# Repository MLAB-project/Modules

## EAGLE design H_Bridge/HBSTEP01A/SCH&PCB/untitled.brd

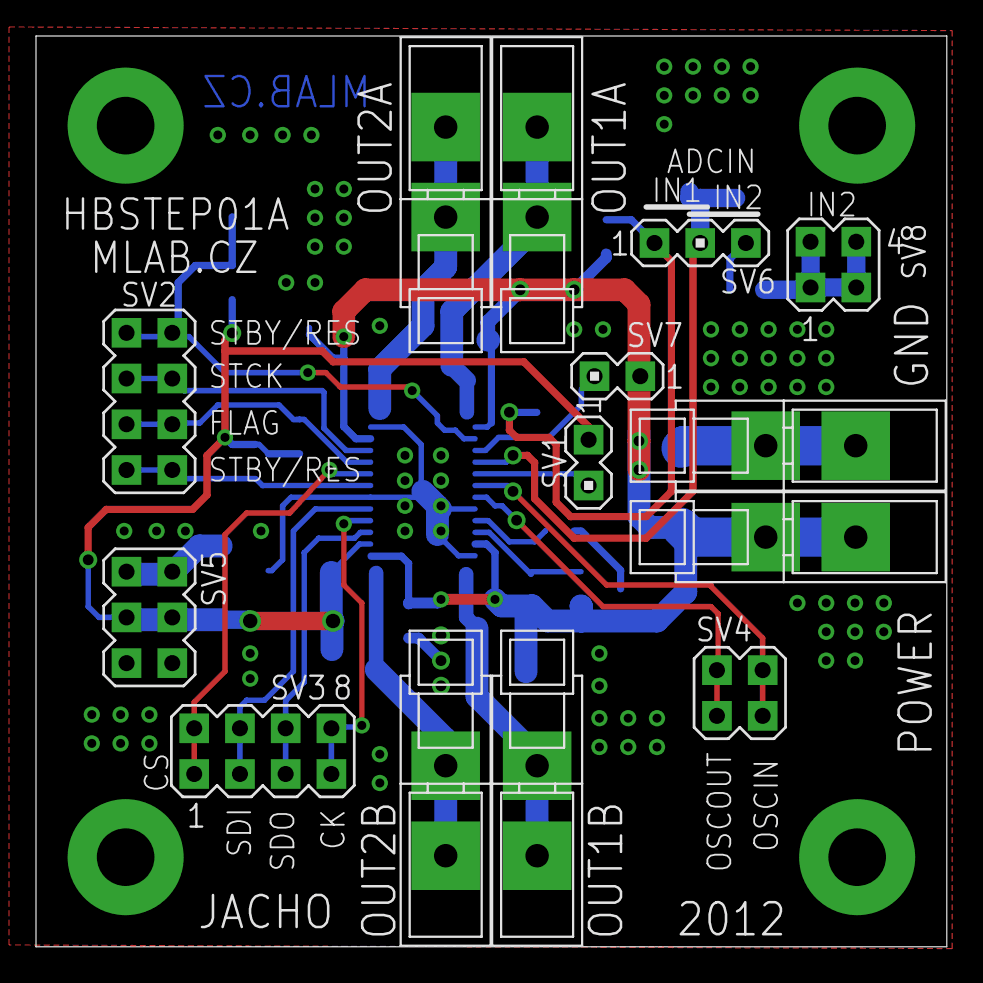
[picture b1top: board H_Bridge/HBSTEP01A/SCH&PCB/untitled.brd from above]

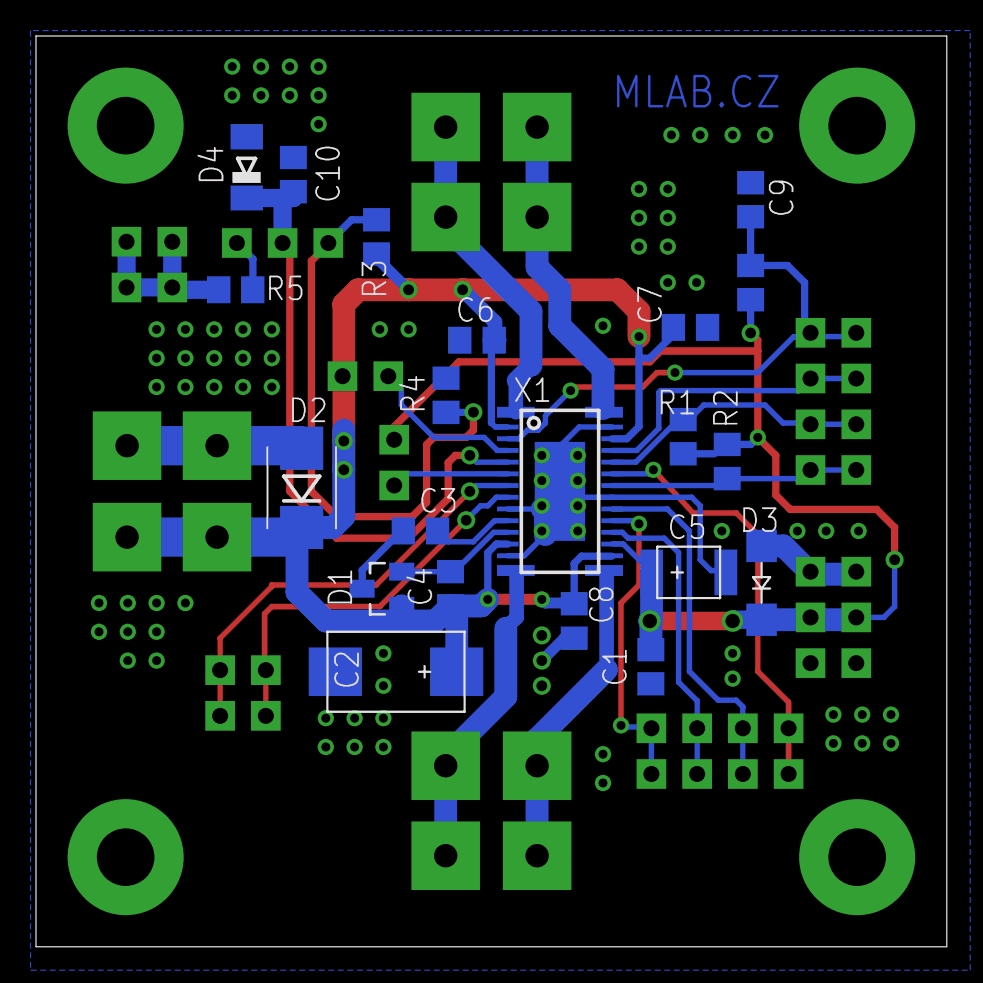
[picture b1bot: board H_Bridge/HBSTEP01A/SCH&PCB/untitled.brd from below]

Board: 2 copper layers, 50.6 x 50.6 mm, 39 parts (21 on the bottom side), 26 nets.

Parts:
C1, C3, C4, C6, C7, C8, C10: C0805
C2: 22M/20V; D
C5: 1M/35V; B
C9: 100p; C0805
CON1, CON2, CON3, CON4, CON5, CON6: WAGO256
D1: SOT23
D2: SMB
D3: SMA
D4: MINIMELF
R1, R2, R3, R4, R5, R5-PULLUP: R0805
SV1, SV7: MA02-1
SV2: MA04-2
SV3: MA04-2@1
SV4: MA02-2
SV5: MA03-2
SV6: MA03-1
SV8: MA02-2@1
X1: HTSSOP28
X3, X4, X5, X6: SROUB3M

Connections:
+12V: C2.+, C4.1, C6.1, C7.1, C8.1, CON6.1, CON6.A1, D1.1, D2.K, R3.2, X1.2, X1.12, X1.16, X1.26
ADCIN: C10.1, D4.C, SV6.2, X1.5
GND: C1.2, C2.-, C5.-, C6.2, C7.2, C8.2, C9.2, C10.2, CON5.1, CON5.A1, D2.A, D3.A, D4.A, R4.1, SV5.1, SV5.2, SV5.5, SV5.6, SV7.1, X1.9, X1.13, X1.21, X1.27, X1.P$1, X3.P$1, X4.P$1, X5.P$1, X6.P$1
unnamed: R1.1, SV2.5, SV2.6, X1.24
unnamed: R2.1, SV2.7, SV2.8, X1.22
unnamed: SV2.3, SV2.4, X1.25
unnamed: C9.1, R5-PULLUP.1, SV2.1, SV2.2, X1.3
unnamed: SV3.1, SV3.2, X1.23
unnamed: SV3.3, SV3.4, X1.20
unnamed: SV3.5, SV3.6, X1.18
unnamed: SV1.2, X1.6
unnamed: SV7.2, X1.4
unnamed: SV4.3, SV4.4, X1.7
unnamed: CON4.1, CON4.A1, X1.28
unnamed: CON3.1, CON3.A1, X1.1
unnamed: CON1.1, CON1.A1, X1.14
unnamed: CON2.1, CON2.A1, X1.15
unnamed: SV4.1, SV4.2, X1.8
unnamed: SV3.7, SV3.8, X1.19
unnamed: R3.1, R4.2, SV6.1
unnamed: R5.2, SV6.3
unnamed: C4.2, D1.2, X1.11
unnamed: C3.2, D1.3
unnamed: C3.1, X1.10
unnamed: R5.1, SV8.1, SV8.2, SV8.3, SV8.4
VCC: C1.1, C5.+, D3.K, R1.2, R2.2, R5-PULLUP.2, SV1.1, SV5.3, SV5.4, X1.17

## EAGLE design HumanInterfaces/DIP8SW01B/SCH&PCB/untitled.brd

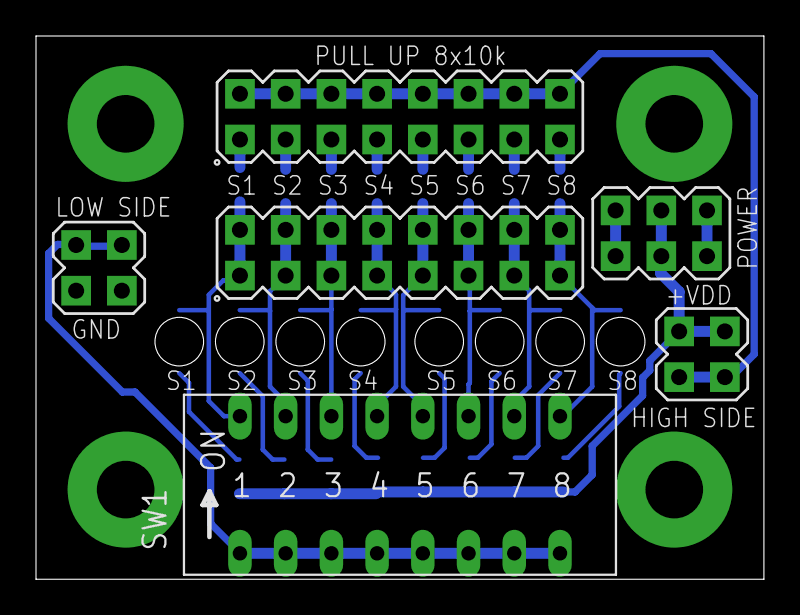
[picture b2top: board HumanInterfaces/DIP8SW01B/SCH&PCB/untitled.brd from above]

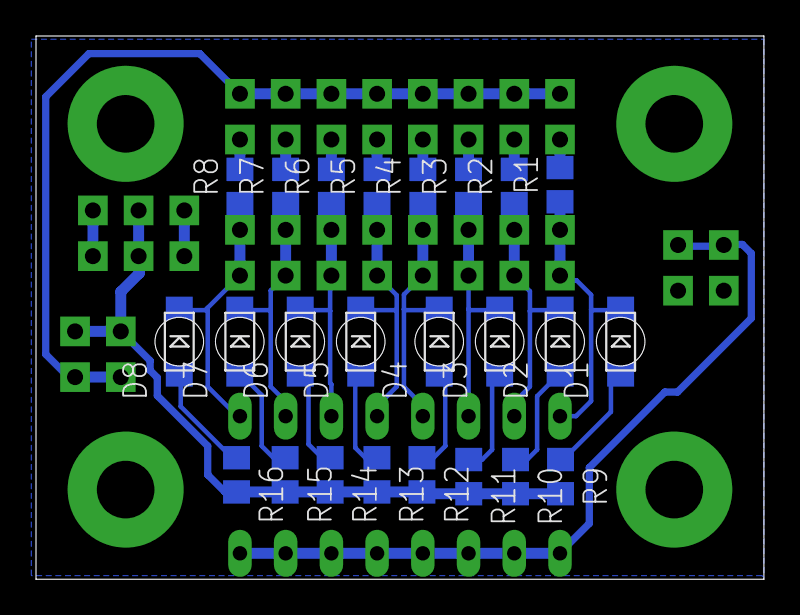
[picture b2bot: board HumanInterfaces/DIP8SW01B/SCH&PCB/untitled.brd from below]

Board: 2 copper layers, 40.4 x 30.2 mm, 34 parts (24 on the bottom side), 28 nets.

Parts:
D1, D2, D3, D4, D5, D6, D7, D8: 1206_2
R1, R2, R3, R4, R5, R6, R7, R8: 10k; 0805
R9, R10, R11, R12, R13, R14, R15, R16: 0805
SV1: MA08-2
SV2, SV4: MA02-2
SV3: MA03-2
SW1: DIP08SW
SW2: MA08-2
X1, X2, X3, X4: SROUB3M

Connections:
GND: SV3.1, SV3.2, SV3.5, SV3.6, SV4.3, SV4.4, X1.P$1, X2.P$1, X3.P$1, X4.P$1
unnamed: D1.K, R1.1, SV1.1, SV1.2, SW1.16
unnamed: D2.K, R2.1, SV1.3, SV1.4, SW1.15
unnamed: D3.K, R3.1, SV1.5, SV1.6, SW1.14
unnamed: D4.K, R4.1, SV1.7, SV1.8, SW1.13
unnamed: D5.K, R5.1, SV1.9, SV1.10, SW1.12
unnamed: D6.K, R6.1, SV1.11, SV1.12, SW1.11
unnamed: D7.K, R7.1, SV1.13, SV1.14, SW1.10
unnamed: D8.K, R8.1, SV1.15, SV1.16, SW1.9
unnamed: R1.2, SW2.1
unnamed: R2.2, SW2.3
unnamed: R3.2, SW2.5
unnamed: R4.2, SW2.7
unnamed: R5.2, SW2.9
unnamed: R6.2, SW2.11
unnamed: R7.2, SW2.13
unnamed: R8.2, SW2.15
unnamed: D2.A, R10.1
unnamed: D3.A, R11.1
unnamed: D4.A, R12.1
unnamed: SV2.1, SV2.2, SW2.2, SW2.4, SW2.6, SW2.8, SW2.10, SW2.12, SW2.14, SW2.16
unnamed: D5.A, R13.1
unnamed: SV4.1, SV4.2, SW1.1, SW1.2, SW1.3, SW1.4, SW1.5, SW1.6, SW1.7, SW1.8
unnamed: D6.A, R14.1
unnamed: D7.A, R15.1
unnamed: D1.A, R9.1
unnamed: D8.A, R16.1
VCC: R9.2, R10.2, R11.2, R12.2, R13.2, R14.2, R15.2, R16.2, SV2.3, SV2.4, SV3.3, SV3.4

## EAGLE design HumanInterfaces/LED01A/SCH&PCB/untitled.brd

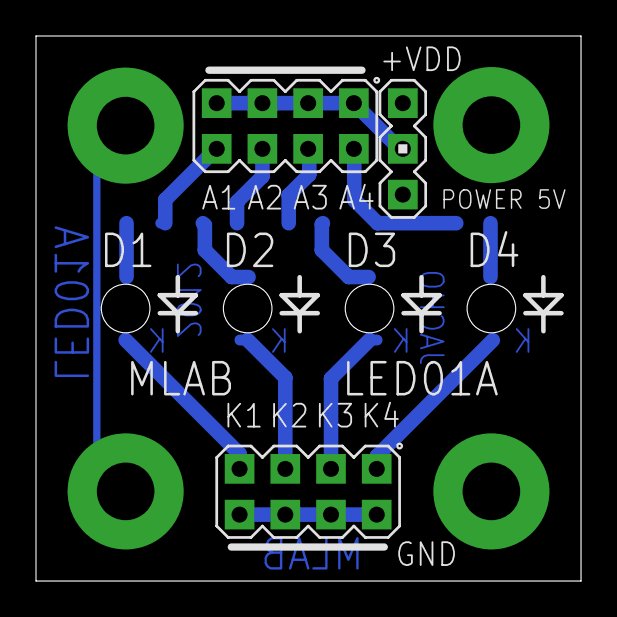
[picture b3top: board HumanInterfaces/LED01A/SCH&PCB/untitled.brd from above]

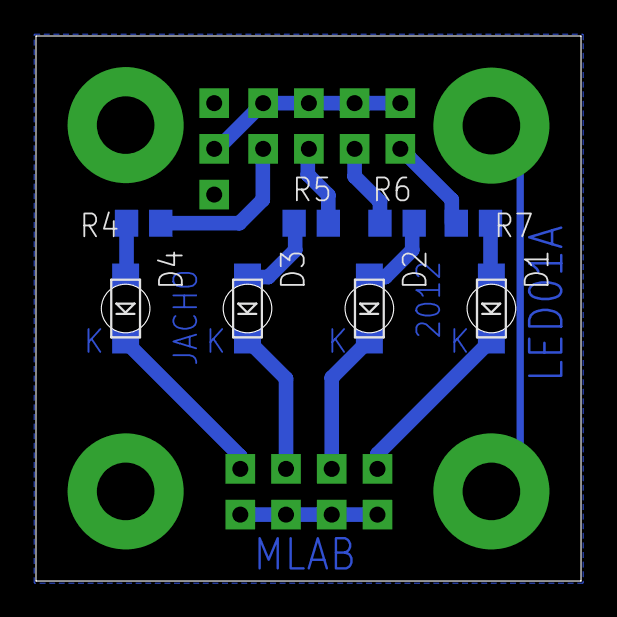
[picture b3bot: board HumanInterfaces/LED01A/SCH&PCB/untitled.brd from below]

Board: 2 copper layers, 30.3 x 30.3 mm, 15 parts (8 on the bottom side), 14 nets.

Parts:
D1, D2, D3, D4: 1206
R4, R5, R6, R7: 0805
SV1, SV2: MA04-2
SV3: MA03-1
X1, X2, X3, X4: SROUB3M

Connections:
GND: SV1.2, SV1.4, SV1.6, SV1.8, SV3.1, SV3.3, X1.P$1, X2.P$1, X3.P$1, X4.P$1
unnamed: D4.K, SV1.1
unnamed: D4.A, R4.1
unnamed: D3.K, SV1.3
unnamed: D2.K, SV1.5
unnamed: D3.A, R5.1
unnamed: D2.A, R6.1
unnamed: D1.A, R7.1
unnamed: R4.2, SV2.2
unnamed: R5.2, SV2.4
unnamed: R6.2, SV2.6
unnamed: D1.K, SV1.7
unnamed: SV2.1, SV2.3, SV2.5, SV2.7, SV3.2
unnamed: R7.2, SV2.8

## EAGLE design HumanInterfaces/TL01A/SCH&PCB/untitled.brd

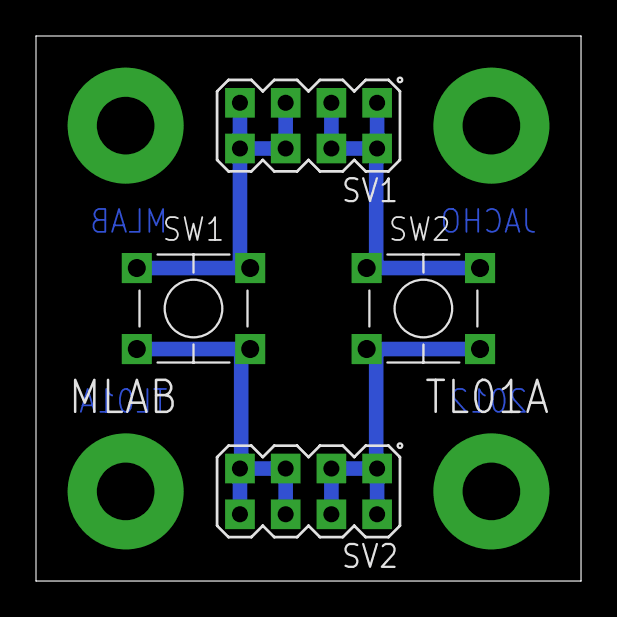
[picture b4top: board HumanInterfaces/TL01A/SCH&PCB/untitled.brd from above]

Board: 2 copper layers, 30.3 x 30.3 mm, 8 parts (0 on the bottom side), 5 nets.

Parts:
SV1, SV2: MA04-2
SW1, SW2: TACT-64K
X1, X2, X3, X4: SROUB3M

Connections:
GND: X1.P$1, X2.P$1, X3.P$1, X4.P$1
unnamed: SV1.5, SV1.6, SV1.7, SV1.8, SW1.P$1, SW1.P$2
unnamed: SV2.5, SV2.6, SV2.7, SV2.8, SW1.P$3, SW1.P$4
unnamed: SV1.1, SV1.2, SV1.3, SV1.4, SW2.P$1, SW2.P$2
unnamed: SV2.1, SV2.2, SV2.3, SV2.4, SW2.P$3, SW2.P$4

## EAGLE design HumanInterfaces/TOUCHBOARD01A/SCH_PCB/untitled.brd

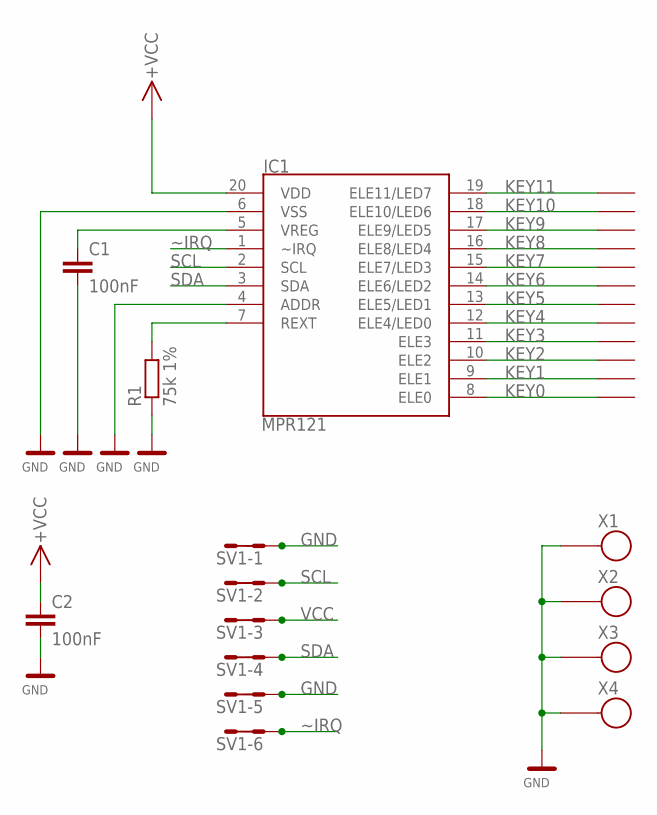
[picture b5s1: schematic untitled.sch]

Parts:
C1, C2: 100nF; C0805
IC1: MPR121; QFN-20-0.4MM
R1: 75k 1%; 0805
SV1: MA06-2
U$1, U$2, U$3, U$4, U$5, U$6, U$7, U$8, U$9, U$10, U$11, U$12: TL_DOTYK_10_15; PLOSKA10_15
X1, X2, X3, X4: SROUB3M

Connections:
GND: C1.2, C2.2, IC1.4 (ADDR), IC1.6 (VSS), R1.1, SV1.1, SV1.2, SV1.9, SV1.10, X1.P$1, X2.P$1, X3.P$1, X4.P$1
KEY0: IC1.8 (ELE0), U$1.P$1
KEY1: IC1.9 (ELE1), U$2.P$1
KEY2: IC1.10 (ELE2), U$3.P$1
KEY3: IC1.11 (ELE3), U$4.P$1
KEY4: IC1.12 (ELE4/LED0), U$5.P$1
KEY5: IC1.13 (ELE5/LED1), U$6.P$1
KEY6: IC1.14 (ELE6/LED2), U$7.P$1
KEY7: IC1.15 (ELE7/LED3), U$8.P$1
KEY8: IC1.16 (ELE8/LED4), U$9.P$1
KEY9: IC1.17 (ELE9/LED5), U$10.P$1
KEY10: IC1.18 (ELE10/LED6), U$11.P$1
KEY11: IC1.19 (ELE11/LED7), U$12.P$1
REXT: IC1.7 (REXT), R1.2
SCL: IC1.2 (SCL), SV1.3, SV1.4
SDA: IC1.3 (SDA), SV1.7, SV1.8
VCC: C2.1, IC1.20 (VDD), SV1.5, SV1.6
VREG: C1.1, IC1.5 (VREG)
~IRQ: IC1.1 (~IRQ), SV1.11, SV1.12

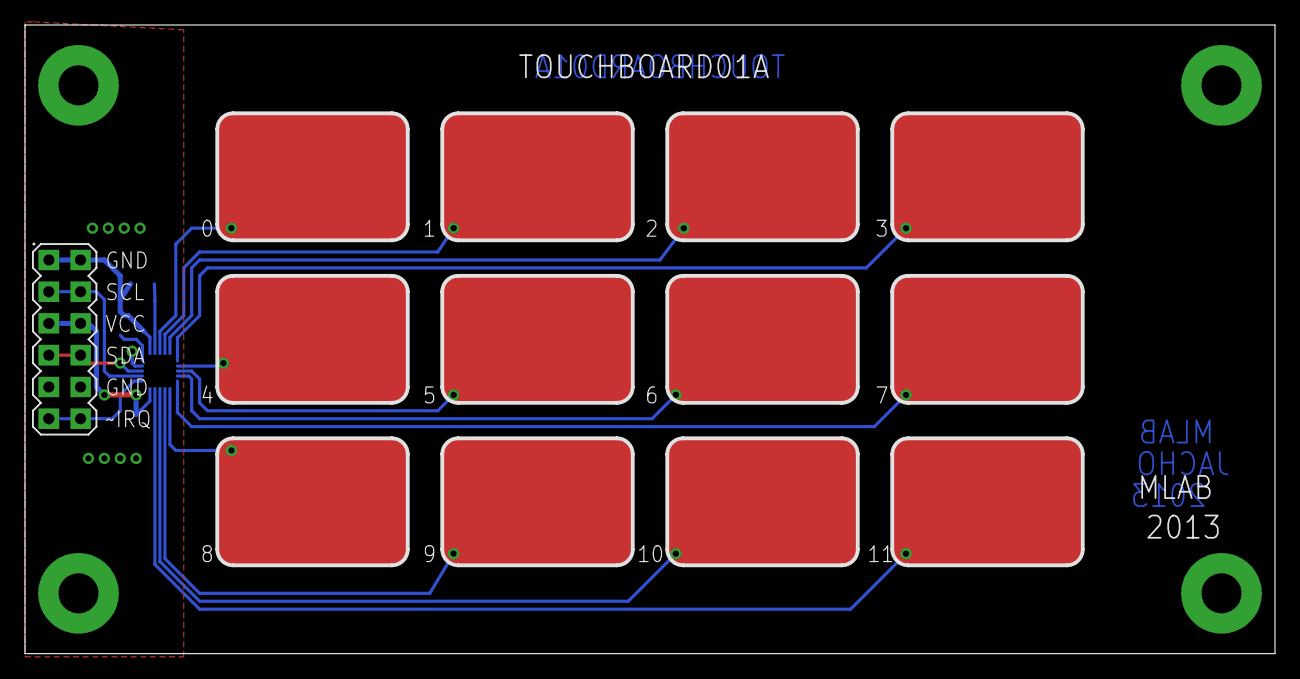
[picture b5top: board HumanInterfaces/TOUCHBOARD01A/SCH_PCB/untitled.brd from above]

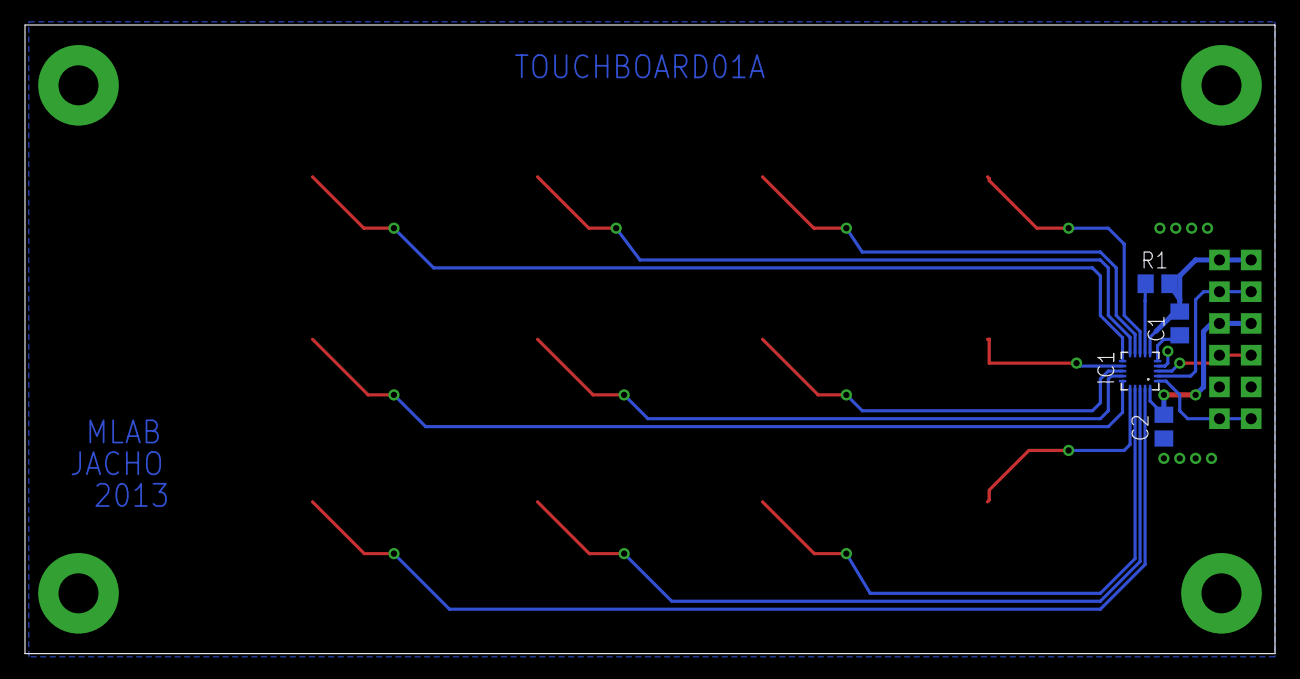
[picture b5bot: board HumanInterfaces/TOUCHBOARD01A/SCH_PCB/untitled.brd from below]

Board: 2 copper layers, 100.0 x 50.3 mm, 21 parts (4 on the bottom side), 19 nets.

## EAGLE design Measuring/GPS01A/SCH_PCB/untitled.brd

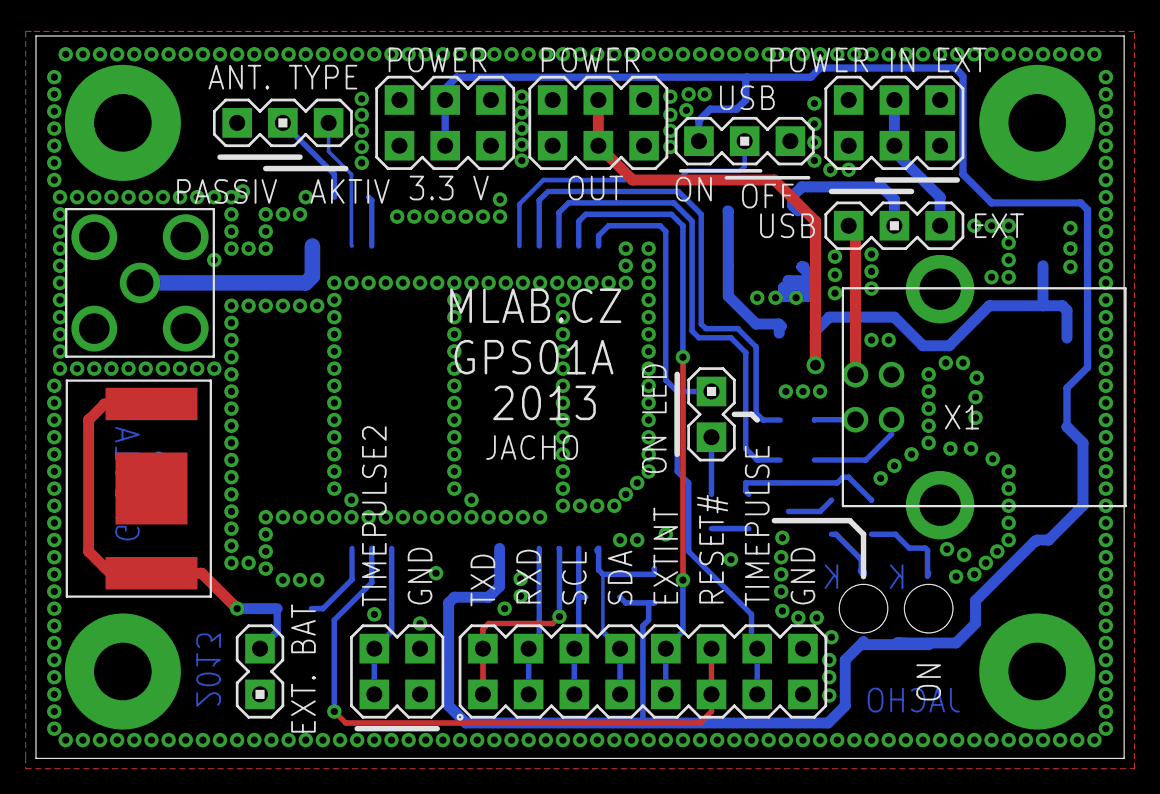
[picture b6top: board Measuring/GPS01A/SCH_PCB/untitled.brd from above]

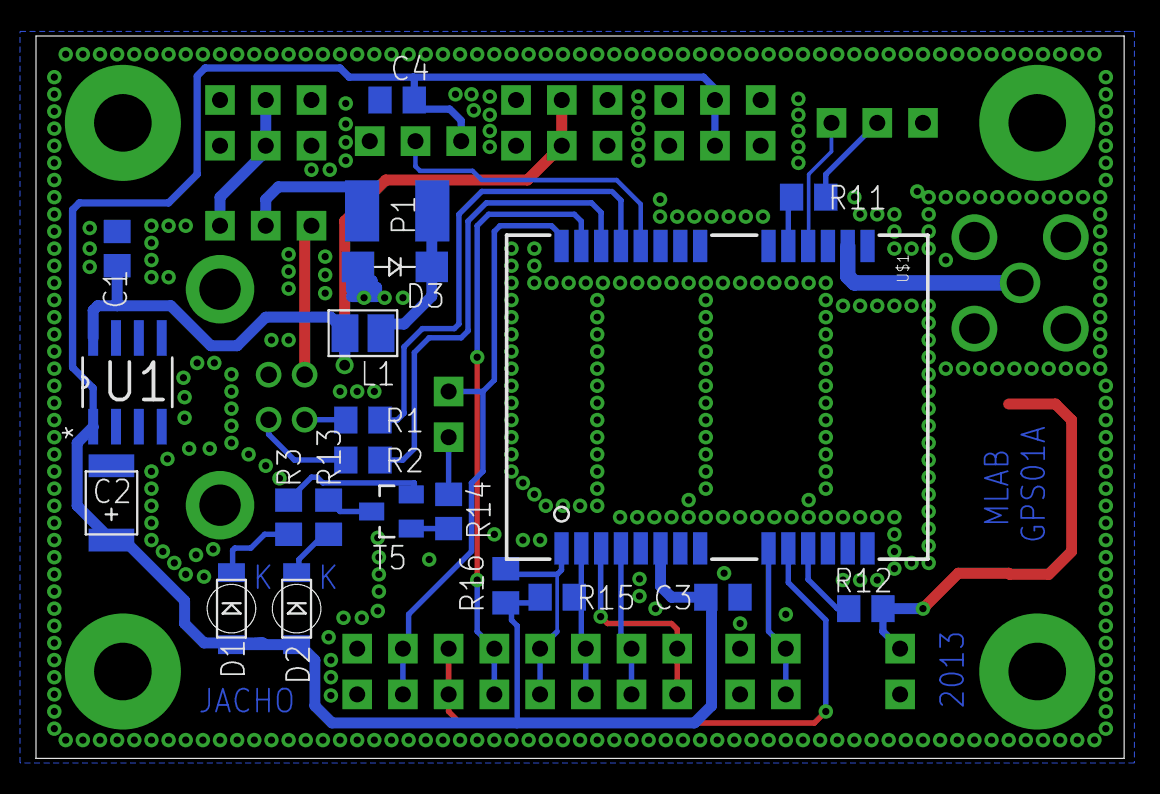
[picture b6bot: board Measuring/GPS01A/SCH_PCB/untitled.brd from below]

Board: 2 copper layers, 60.5 x 40.1 mm, 38 parts (21 on the bottom side), 31 nets.

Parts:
C1, C3, C4: 100nF; C0805
C2: 10uF; B
D1: CERVENA; 1206
D2: ZELENA; 1206
D3: SMA
L1: 1210
P1: 1812
R1, R2: 33; 0805
R3, R13: 150R; 0805
R11: 10; 0805
R12: 100; 0805
R14: 0805
R15, R16: 4k7; 0805
SV1, SV4, SV8: MA03-1
SV2, SV9, SV10: MA03-2
SV3, SV7: MA02-1
SV5: MA02-2
SV6: MA08-2
SW1: 1.55V; BAT6MM8
SW2: SMA
T5: BC817; SOT23
U1: LE33CD-TR; SOIC127P600X175-8N
U$1: UBLOX-LEA-6
X1: USB_B
X2, X3, X4, X5: SROUB3M

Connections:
+3.3V: C2.+, C3.1, C4.1, D1.A, D2.A, R15.2, R16.2, SV8.1, SV9.3, SV9.4, U1.1, U$1.6
EXTINT: SV6.9, SV6.10, U$1.27
GND: C1.2, C2.-, C3.2, C4.2, D3.A, R3.1, SV2.1, SV2.2, SV2.5, SV2.6, SV3.2, SV4.1, SV5.3, SV5.4, SV6.15, SV6.16, SV8.3, SV9.1, SV9.2, SV9.5, SV9.6, SV10.1, SV10.2, SV10.5, SV10.6, SW1.-, SW2.-1, SW2.-2, SW2.-3, SW2.-4, T5.2, U1.2, U1.3, U1.5, U1.6, U1.7, U$1.7, U$1.13, U$1.14, U$1.15, U$1.17, X1.4, X1.GND, X1.GND2, X2.P$1, X3.P$1, X4.P$1, X5.P$1
unnamed: SW2.+, U$1.16
unnamed: SV1.1, SV2.3, SV2.4
unnamed: R1.1, X1.2
unnamed: R2.1, X1.3
unnamed: C1.1, L1.P$2, SV10.3, SV10.4, U1.8
unnamed: P1.2, SV1.2
unnamed: D1.K, R3.2
unnamed: R11.2, U$1.19
unnamed: D3.K, L1.P$1, P1.1
unnamed: R11.1, SV4.2
unnamed: R12.1, U$1.11
unnamed: R12.2, SV3.1, SW1.1+, SW1.2+
unnamed: SV5.1, SV5.2, U$1.9
unnamed: D2.K, R13.2
unnamed: R13.1, T5.3
unnamed: R14.2, T5.1
unnamed: R14.1, SV7.1
RESET_N: SV6.11, SV6.12, U$1.10
RXD: SV6.3, SV6.4, U$1.4
SCL: R15.1, SV6.5, SV6.6, U$1.2
SDA: R16.1, SV6.7, SV6.8, U$1.1
TIMEPULSE: SV6.13, SV6.14, SV7.2, U$1.28
TXD: SV6.1, SV6.2, U$1.3
USB_DET: SV8.2, U$1.24
USB_DM: R1.2, U$1.25
USB_DP: R2.2, U$1.26
VCC_RF: SV4.3, U$1.18
VDD_USB: SV1.3, X1.1

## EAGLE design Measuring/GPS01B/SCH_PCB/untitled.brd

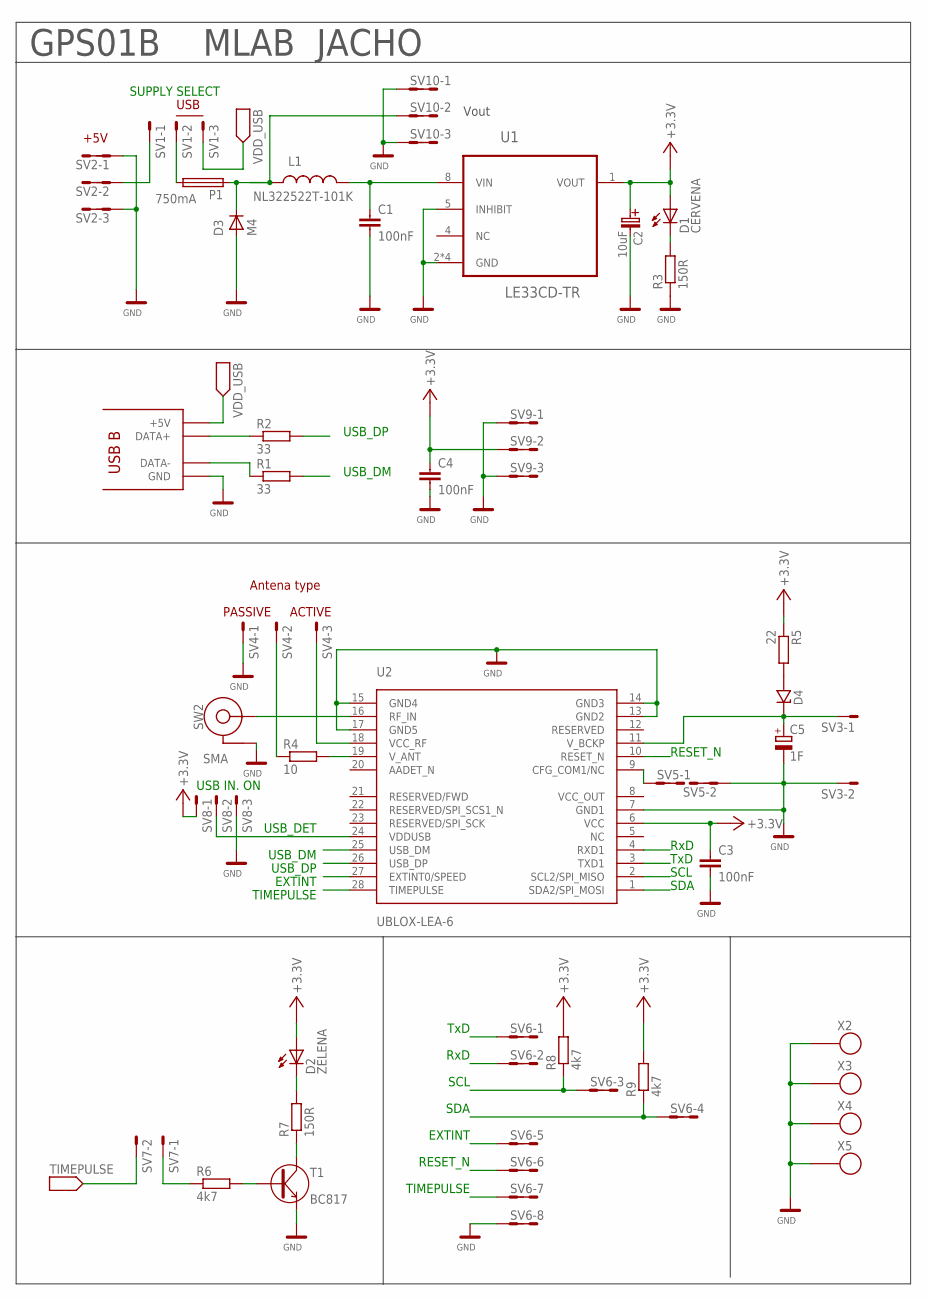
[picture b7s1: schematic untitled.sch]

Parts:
C1, C3, C4: 100nF; C0805
C2: 10uF; B
C5: 1F; E3,5-8
D1: CERVENA; 1206
D2: ZELENA; 1206
D3: M4; SMA
D4: D-ZENEROVA; MINIMELF
L1: NL322522T-101K; 1210
P1: 750mA; 1812
R1, R2: 33; 0805
R3, R7: 150R; 0805
R4: 10; 0805
R5: 22; 0805
R6, R8, R9: 4k7; 0805
SV1, SV4, SV8: MA03-1
SV2, SV9, SV10: MA03-2
SV3, SV7: MA02-1
SV5: MA02-2
SV6: MA08-2
SW2: SMA
T1: BC817; SOT23
U1: LE33CD-TR; SOIC127P600X175-8N
U2: UBLOX-LEA-6
X1: USB_B
X2, X3, X4, X5: SROUB3M

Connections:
+3.3V: C2.+ (C_EL+), C3.1, C4.1, D1.A, D2.A, R5.1, R8.2, R9.2, SV8.1, SV9.3, SV9.4, U1.1 (VOUT), U2.6 (VCC)
EXTINT: SV6.9, SV6.10, U2.27 (EXTINT0/SPEED)
GND: C1.2, C2.- (C_EL-), C3.2, C4.2, C5.-, D3.A, R3.1, SV2.1, SV2.2, SV2.5, SV2.6, SV3.2, SV4.1, SV5.3, SV5.4, SV6.15, SV6.16, SV8.3, SV9.1, SV9.2, SV9.5, SV9.6, SV10.1, SV10.2, SV10.5, SV10.6, SW2.-1 (-), SW2.-2 (-), SW2.-3 (-), SW2.-4 (-), T1.2 (E), U1.2 (GND), U1.3 (GND), U1.5 (INHIBIT), U1.6 (GND), U1.7 (GND), U2.7 (GND1), U2.13 (GND2), U2.14 (GND3), U2.15 (GND4), U2.17 (GND5), X1.4 (GND), X1.GND, X1.GND2 (GND), X2.P$1, X3.P$1, X4.P$1, X5.P$1
unnamed: SW2.+, U2.16 (RF_IN)
unnamed: SV1.1, SV2.3, SV2.4
unnamed: R1.1, X1.2 (DATA-)
unnamed: R2.1, X1.3 (DATA+)
unnamed: C1.1, L1.P$2 (2), U1.8 (VIN)
unnamed: D4.A, R5.2
unnamed: P1.2, SV1.2
unnamed: D3.K (C), L1.P$1 (1), P1.1, SV10.3, SV10.4
unnamed: D1.K (C), R3.2
unnamed: R4.2, U2.19 (V_ANT)
unnamed: R4.1, SV4.2
unnamed: C5.+, D4.C (K), SV3.1, U2.11 (V_BCKP)
unnamed: SV5.1, SV5.2, U2.9 (CFG_COM1/NC)
unnamed: D2.K (C), R7.2
unnamed: R7.1, T1.3 (C)
unnamed: R6.2, T1.1 (B)
unnamed: R6.1, SV7.1
RESET_N: SV6.11, SV6.12, U2.10 (RESET_N)
RXD: SV6.3, SV6.4, U2.4 (RXD1)
SCL: R8.1, SV6.5, SV6.6, U2.2 (SCL2/SPI_MISO)
SDA: R9.1, SV6.7, SV6.8, U2.1 (SDA2/SPI_MOSI)
TIMEPULSE: SV6.13, SV6.14, SV7.2, U2.28 (TIMEPULSE)
TXD: SV6.1, SV6.2, U2.3 (TXD1)
USB_DET: SV8.2, U2.24 (VDDUSB)
USB_DM: R1.2, U2.25 (USB_DM)
USB_DP: R2.2, U2.26 (USB_DP)
VCC_RF: SV4.3, U2.18 (VCC_RF)
VDD_USB: SV1.3, X1.1 (+5V)

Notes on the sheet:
USB_DM
USB_DP
USB
+5V
TxD
RxD
Antena type
ACTIVE
PASSIVE
USB_DET
EXTINT
TIMEPULSE
RESET_N
SCL
SDA
SUPPLY SELECT
GPS01B
MLAB
JACHO
USB IN. ON
Vout

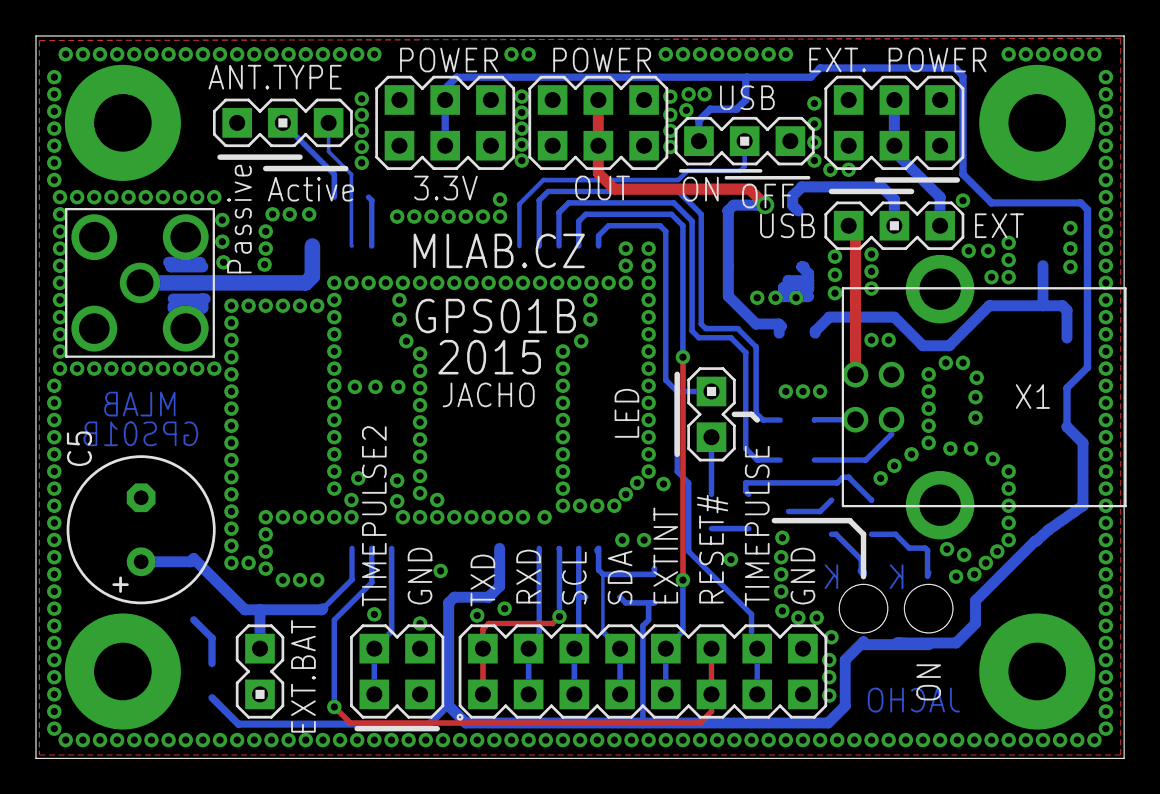
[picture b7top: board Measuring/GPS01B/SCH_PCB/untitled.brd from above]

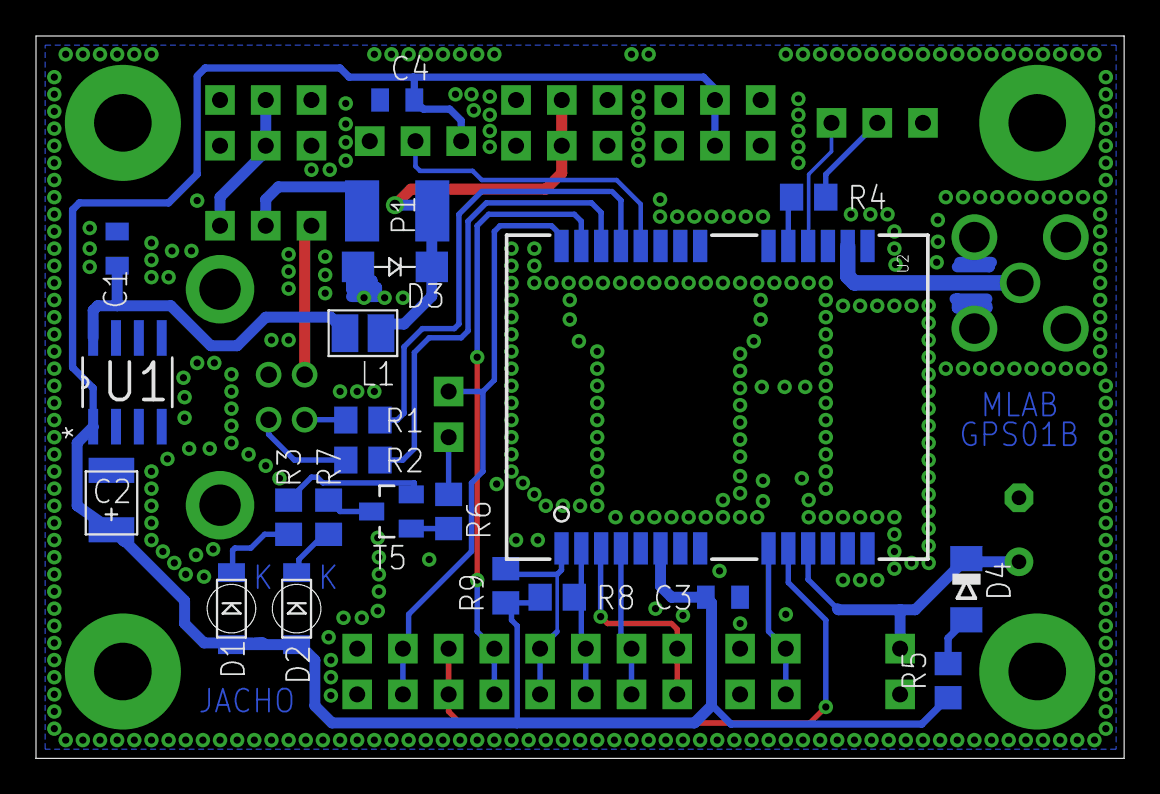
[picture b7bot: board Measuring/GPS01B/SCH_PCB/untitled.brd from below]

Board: 2 copper layers, 60.5 x 40.1 mm, 39 parts (22 on the bottom side), 31 nets.

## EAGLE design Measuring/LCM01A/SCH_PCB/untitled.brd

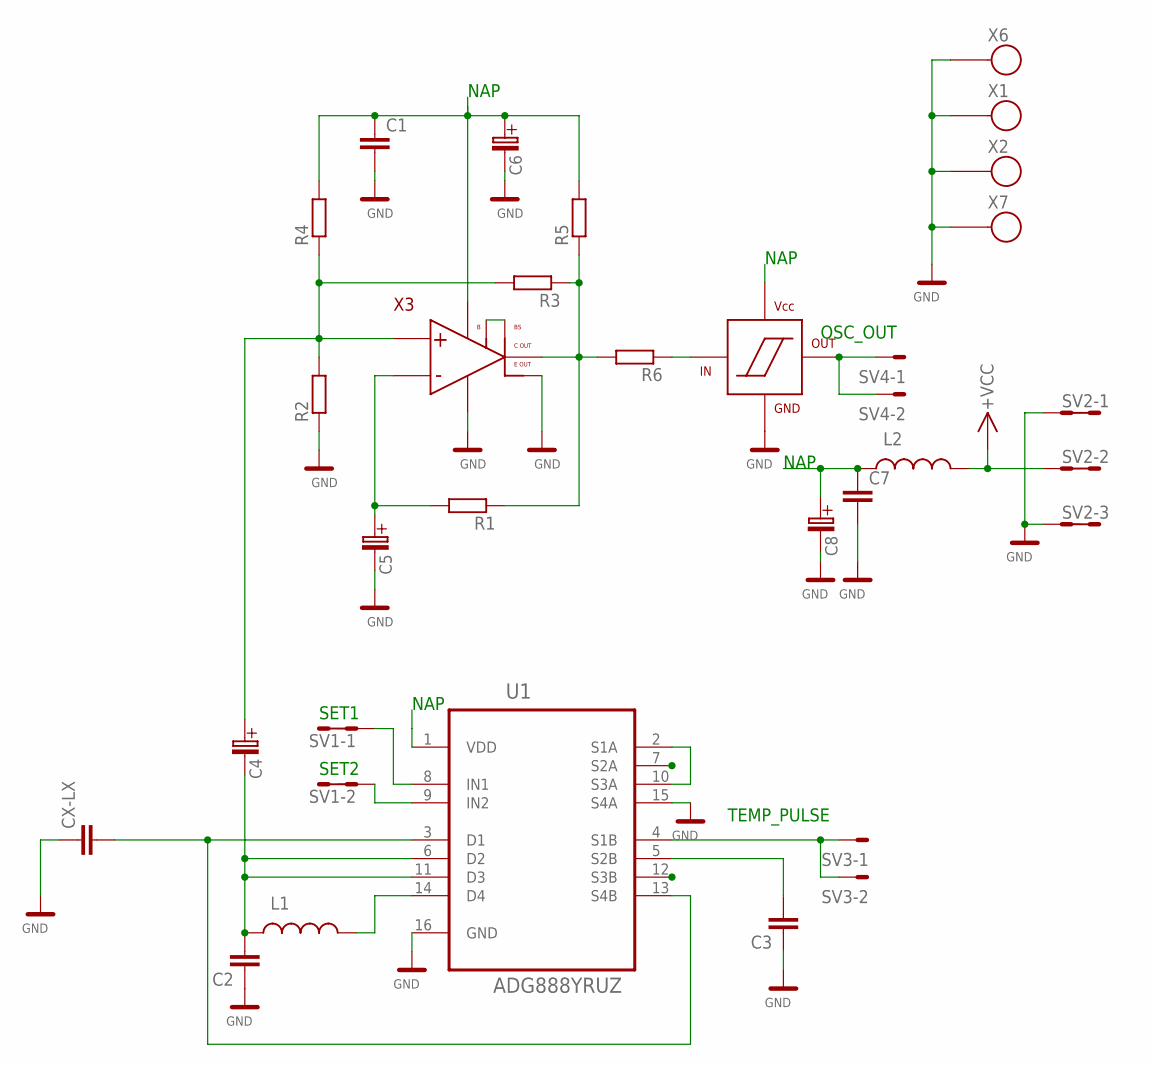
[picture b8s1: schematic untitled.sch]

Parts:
C1, C2, C3, C7: C0805
C4, C5, C6, C8: B
CX-LX: C0805
L1, L2: L1210; 1210
R1, R2, R3, R4, R5, R6: R0805; 0805
SV1: MA02-2
SV2: MA03-2
SV3, SV4: MA02-1
U1: ADG888YRUZ; SOP65P640X120-16N
X1, X2, X6, X7: SROUB3M
X3: LM311; SO8
X4: 74HC1G14; SOT353

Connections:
C+: CX-LX.2, U1.3 (D1), U1.13 (S4B)
GND: C1.2, C2.1, C3.1, C5.- (C_EL-), C6.- (C_EL-), C7.2, C8.- (C_EL-), CX-LX.1, R2.1, SV2.1, SV2.2, SV2.5, SV2.6, U1.15 (S4A), U1.16 (GND), X1.P$1, X2.P$1, X3.1 (E_OUT), X3.4 (GND), X4.3 (GND), X6.P$1, X7.P$1
unnamed: C2.2, C4.- (C_EL-), L1.P$1 (1), U1.6 (D2), U1.11 (D3)
unnamed: X3.5 (B), X3.6 (BS)
unnamed: C3.2, U1.5 (S2B)
unnamed: U1.2 (S1A), U1.10 (S3A)
unnamed: SV1.1, SV1.2, U1.8 (IN1)
unnamed: SV3.1, SV3.2, U1.4 (S1B)
unnamed: L1.P$2 (2), U1.14 (D4)
unnamed: C5.+ (C_EL+), R1.2, X3.3 (-)
unnamed: R1.1, R3.1, R5.1, R6.2, X3.7 (VOUT)
unnamed: SV1.3, SV1.4, U1.9 (IN2)
unnamed: R6.1, X4.2 (IN)
unnamed: C4.+ (C_EL+), R2.2, R3.2, R4.1, X3.2 (+)
unnamed: SV4.1, SV4.2, X4.4 (OUT)
NAP: C1.1, C6.+ (C_EL+), C7.1, C8.+ (C_EL+), L2.P$1 (1), R4.2, R5.2, U1.1 (VDD), X3.8 (VDD), X4.5 (VCC)
VCC: L2.P$2 (2), SV2.3, SV2.4

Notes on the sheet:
OSC_OUT
SET1
SET2
TEMP_PULSE
NAP

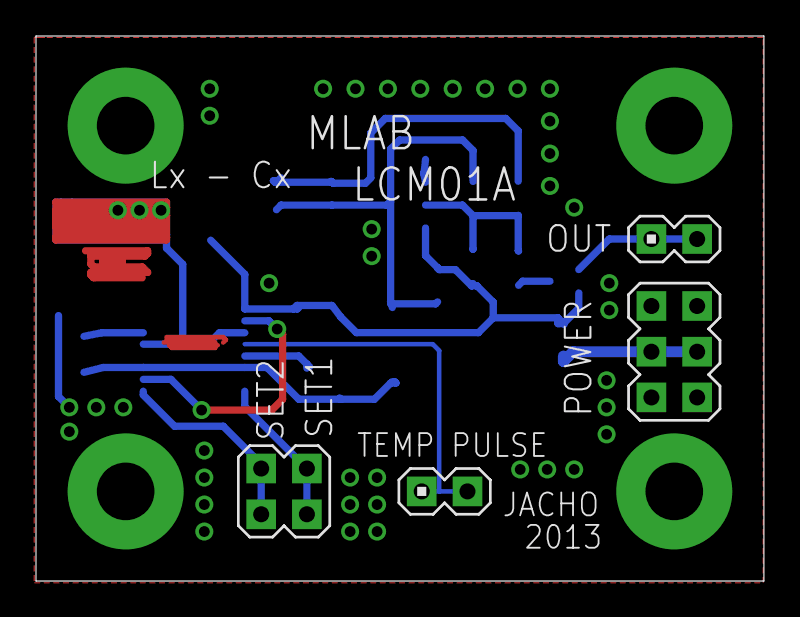
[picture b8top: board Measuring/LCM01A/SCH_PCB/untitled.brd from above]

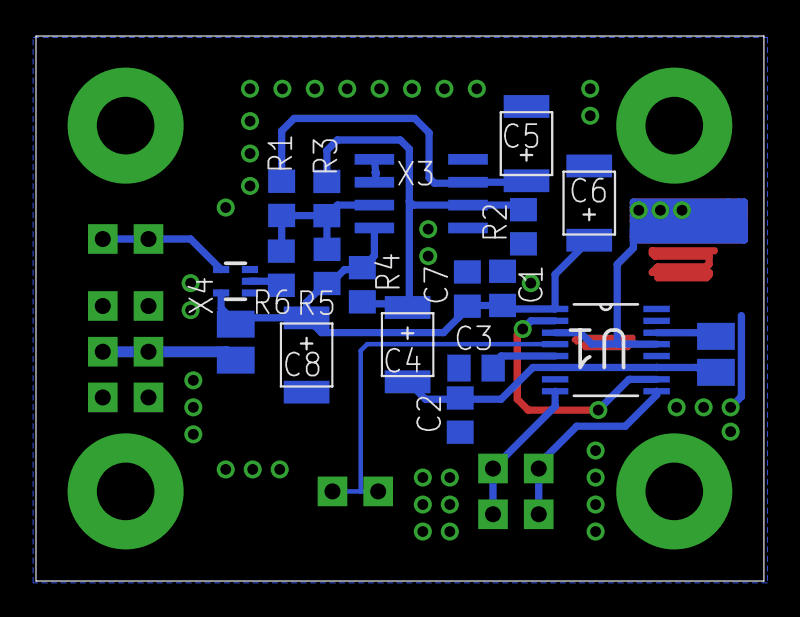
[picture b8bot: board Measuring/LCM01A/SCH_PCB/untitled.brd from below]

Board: 2 copper layers, 40.4 x 30.3 mm, 28 parts (19 on the bottom side), 17 nets.

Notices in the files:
parts and their libraries:
PaJa_C-tantal_SMD: Copyright (C) PaJa 2009
PaJa_22: Copyright (C) PaJa 2001-2010
SparkFun: Licensing: CC v3.0 Share-Alike You are welcome to use this library for commercial purposes.
